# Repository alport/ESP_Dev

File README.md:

# ESP_Dev
ESP8266 dev board for ESP07/12

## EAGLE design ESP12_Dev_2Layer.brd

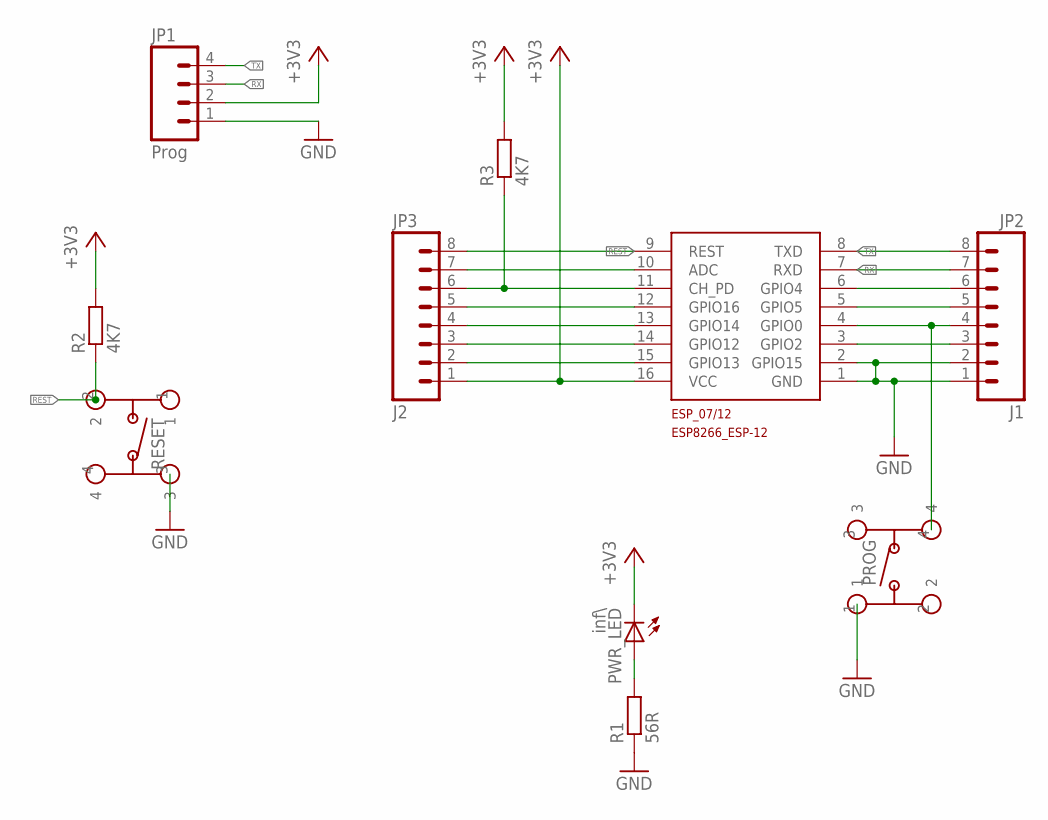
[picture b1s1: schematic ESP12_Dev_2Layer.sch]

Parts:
ESP_07/12: ESP8266_ESP-12; ESP8266-ESP12
JP1: Prog; 1X04_LOCK
JP2: J1; 1X08_LOCK
JP3: J2; 1X08_LOCK
PROG: TACTILE-SWITCH-SMD
PWR_LED: inf\; CHIPLED_0805
R1: 56R; R0805
R2, R3: 4K7; R0805
RESET: TACTILE-SWITCH-SMD

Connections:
+3V3: ESP_07/12.16 (VCC), JP1.2, JP3.1, PWR_LED.C, R2.2, R3.2
ADC: ESP_07/12.10 (ADC), JP3.7
CH_PD: ESP_07/12.11 (CH_PD), JP3.6, R3.1
GND: ESP_07/12.1 (GND), ESP_07/12.2 (GPIO15), JP1.1, JP2.1, JP2.2, PROG.1, R1.1, RESET.3
GPIO0: ESP_07/12.4 (GPIO0), JP2.4, PROG.4
GPIO2: ESP_07/12.3 (GPIO2), JP2.3
GPIO4: ESP_07/12.6 (GPIO4), JP2.6
GPIO5: ESP_07/12.5 (GPIO5), JP2.5
GPIO12: ESP_07/12.14 (GPIO12), JP3.3
GPIO13: ESP_07/12.15 (GPIO13), JP3.2
GPIO14: ESP_07/12.13 (GPIO14), JP3.4
GPIO16: ESP_07/12.12 (GPIO16), JP3.5
unnamed: PWR_LED.A, R1.2
REST: ESP_07/12.9 (REST), JP3.8, R2.1, RESET.2
RX: ESP_07/12.7 (RXD), JP1.3, JP2.7
TX: ESP_07/12.8 (TXD), JP1.4, JP2.8

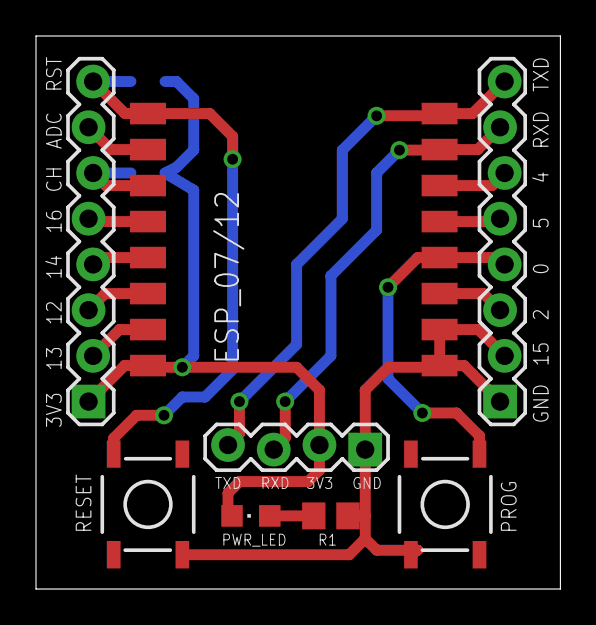
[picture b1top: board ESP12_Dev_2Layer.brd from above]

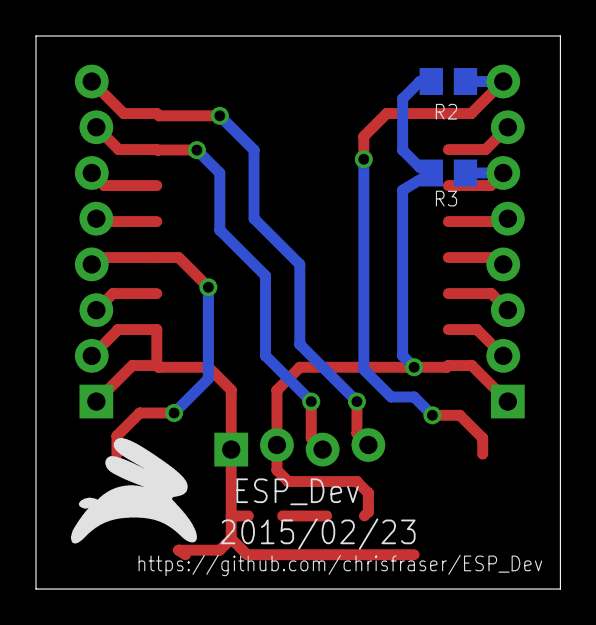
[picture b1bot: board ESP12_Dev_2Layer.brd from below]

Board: 2 copper layers, 29.1 x 30.7 mm, 11 parts (3 on the bottom side), 16 nets.

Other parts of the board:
U$1: GWAJA-LOGO-PLACE

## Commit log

2015-02-23 Version one
2015-02-23 initial
2015-02-23 Added two layer option
    Committer: Chris Fraser <hello@chrisfraser.co.za>

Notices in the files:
parts and their libraries:
SparkFun-Connectors: Licensing: Creative Commons ShareAlike 4.0 International - https://creativecommons.org/licenses/by-sa/4.0
